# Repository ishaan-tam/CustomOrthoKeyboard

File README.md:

# CustomOrthoKeyboard

A customizable 4x12 ortholinear keyboard powered by Zephyr RTOS, with support for custom shields, layouts, and future expansions.

## Features
- 4x12 ortholinear layout
- Zephyr-based firmware
- Custom keymaps and debounce tuning
- QMK-inspired structure
- USB input with hot-plug detection

## Folder Overview
- `boards/shields/`: Custom shield definitions and pin configs
- `config/`: Keymap and build configs for the keyboard
- `zephyr/`: Zephyr OS base setup
- `build.yaml`: Build process definition

## Getting Started
To build the firmware:
```bash
west init -l .
west update
west build -b <your_board> -p

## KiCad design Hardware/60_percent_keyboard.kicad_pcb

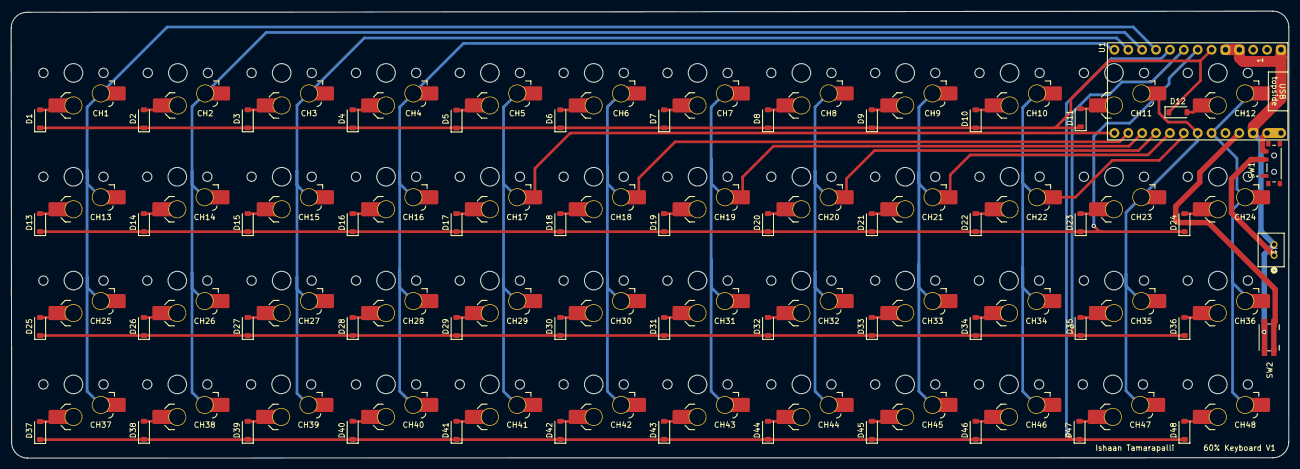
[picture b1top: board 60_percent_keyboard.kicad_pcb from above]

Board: 2 copper layers, 233.8 x 81.8 mm, 100 parts (0 on the bottom side), 68 nets.

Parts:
CH1, CH2, CH3, CH4, CH5, CH6, CH7, CH8, CH9, CH10, CH11, CH12, CH13, CH14, CH15, CH16, CH17, CH18, CH19, CH20, CH21, CH22, CH23, CH24, CH25, CH26, CH27, CH28, CH29, CH30, CH31, CH32, CH33, CH34, CH35, CH36, CH37, CH38, CH39, CH40, CH41, CH42, CH43, CH44, CH45, CH46, CH47, CH48: choc_SW_solder; SW_choc_v1_HS_1u
D1, D2, D3, D4, D5, D6, D7, D8, D9, D10, D11, D12, D13, D14, D15, D16, D17, D18, D19, D20, D21, D22, D23, D24, D25, D26, D27, D28, D29, D30, D31, D32, D33, D34, D35, D36, D37, D38, D39, D40, D41, D42, D43, D44, D45, D46, D47, D48: D; D_SOD-123
J1: Conn_01x02_Socket; CONN2_B2B-PH-K-S_JST
SW1: SW_SPDT; SW_EG1215AA
SW2: SW_Push; Panasonic_EVQPUJ_EVQPUA
U1: nice_nano; nice_nano_AH_USBup

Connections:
BAT+: SW1.3 (C), U1.13 (BAT+), U1.29 (BAT+)
GND: J1.2, SW2.2, U1.3 (GND), U1.4 (GND), U1.14 (GND), U1.28 (GND)
unnamed: CH1.2, D1.2 (A)
unnamed: CH2.2, D2.2 (A)
unnamed: CH3.2, D3.2 (A)
unnamed: CH4.2, D4.2 (A)
unnamed: CH5.2, D5.2 (A)
unnamed: CH6.2, D6.2 (A)
unnamed: CH7.2, D7.2 (A)
unnamed: CH8.2, D8.2 (A)
unnamed: CH9.2, D9.2 (A)
unnamed: CH10.2, D10.2 (A)
unnamed: CH11.2, D11.2 (A)
unnamed: CH12.2, D12.2 (A)
unnamed: CH13.2, D13.2 (A)
unnamed: CH14.2, D14.2 (A)
unnamed: CH15.2, D15.2 (A)
unnamed: CH16.2, D16.2 (A)
unnamed: CH17.2, D17.2 (A)
unnamed: CH18.2, D18.2 (A)
unnamed: CH19.2, D19.2 (A)
unnamed: CH20.2, D20.2 (A)
unnamed: CH21.2, D21.2 (A)
unnamed: CH22.2, D22.2 (A)
unnamed: CH23.2, D23.2 (A)
unnamed: CH24.2, D24.2 (A)
unnamed: CH25.2, D25.2 (A)
unnamed: CH26.2, D26.2 (A)
unnamed: CH27.2, D27.2 (A)
unnamed: CH28.2, D28.2 (A)
unnamed: CH29.2, D29.2 (A)
unnamed: CH30.2, D30.2 (A)
unnamed: CH31.2, D31.2 (A)
unnamed: CH32.2, D32.2 (A)
unnamed: CH33.2, D33.2 (A)
unnamed: CH34.2, D34.2 (A)
unnamed: CH35.2, D35.2 (A)
unnamed: CH36.2, D36.2 (A)
unnamed: CH37.2, D37.2 (A)
unnamed: CH38.2, D38.2 (A)
unnamed: CH39.2, D39.2 (A)
unnamed: CH40.2, D40.2 (A)
unnamed: CH41.2, D41.2 (A)
unnamed: CH42.2, D42.2 (A)
unnamed: CH43.2, D43.2 (A)
unnamed: CH44.2, D44.2 (A)
unnamed: CH45.2, D45.2 (A)
unnamed: CH46.2, D46.2 (A)
unnamed: CH47.2, D47.2 (A)
unnamed: CH48.2, D48.2 (A)
RAW: J1.1, SW1.2 (B)
RST: SW2.1, U1.15 (RST)
col1: CH1.1, CH13.1, CH25.1, CH37.1, U1.9 (P1.00)
col2: CH2.1, CH14.1, CH26.1, CH38.1, U1.10 (P0.11)
col3: CH3.1, CH15.1, CH27.1, CH39.1, U1.11 (P1.04-LF)
col4: CH4.1, CH16.1, CH28.1, CH40.1, U1.12 (P1.06-LF)
col5: CH5.1, CH17.1, CH29.1, CH41.1, U1.24 (P0.09-LF)
col6: CH6.1, CH18.1, CH30.1, CH42.1, U1.23 (P0-10-LF)
col7: CH7.1, CH19.1, CH31.1, CH43.1, U1.22 (P1.11-LF)
col8: CH8.1, CH20.1, CH32.1, CH44.1, U1.21 (P1.13-LF)
col9: CH9.1, CH21.1, CH33.1, CH45.1, U1.20 (P1.15-LF)
col10: CH10.1, CH22.1, CH34.1, CH46.1, U1.19 (P0.02-LF)
col11: CH11.1, CH23.1, CH35.1, CH47.1, U1.18 (P0.29-LF)
col12: CH12.1, CH24.1, CH36.1, CH48.1, U1.17 (P0.31-LF)
row1: D1.1 (K), D2.1 (K), D3.1 (K), D4.1 (K), D5.1 (K), D6.1 (K), D7.1 (K), D8.1 (K), D9.1 (K), D10.1 (K), D11.1 (K), D12.1 (K), U1.5 (P0.17)
row2: D13.1 (K), D14.1 (K), D15.1 (K), D16.1 (K), D17.1 (K), D18.1 (K), D19.1 (K), D20.1 (K), D21.1 (K), D22.1 (K), D23.1 (K), D24.1 (K), U1.6 (P0.20)
row3: D25.1 (K), D26.1 (K), D27.1 (K), D28.1 (K), D29.1 (K), D30.1 (K), D31.1 (K), D32.1 (K), D33.1 (K), D34.1 (K), D35.1 (K), D36.1 (K), U1.7 (P0.22)
row4: D37.1 (K), D38.1 (K), D39.1 (K), D40.1 (K), D41.1 (K), D42.1 (K), D43.1 (K), D44.1 (K), D45.1 (K), D46.1 (K), D47.1 (K), D48.1 (K), U1.8 (P0.24)

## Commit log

2024-07-27 Initial User Config.
2024-07-27 small change
2024-07-27 added files
2024-07-27 more changes
2024-07-27 added more files
2024-07-27 naming fix
2024-07-28 simplified to a 2x4 matrix
2024-07-28 simplified to a 2x4 matrix, used gpt this time
2024-07-28 back to known good
2024-07-28 changed to row2col
2024-07-28 changed pin assignments
2024-07-28 reverted back
2024-07-28 switched col and rows
2024-07-28 single key
2024-07-28 single key (fixed col and row assignemnt)
2024-07-28 swapped rows and columns
2024-07-28 swapped rows and colums
2024-07-28 trying differnt pins
2024-07-28 changed row to GPIO_ACTIVE_HIGH | GPIO_PULL_DOWN
2024-07-28 chagned pin number
2024-07-28 pins look right, changed to row2col
2024-07-28 swapped pull down for rows and cols
2024-07-28 keyboard worked only when connected to a multimeter set to continuity at the same time
2024-07-28 changed to 2x4 matrix
2024-07-28 fixed no of declared rows
2024-07-28 fixed row and col gpios
2024-07-28 changed to 2x3 matrix
2024-07-28 trying top right key
2024-07-28 trying row-gpio active high
2024-07-28 changed to col2row
2024-07-28 trying different pin
2024-07-28 changed pin again
2024-07-28 changed col to pull up
2024-09-30 reverted back to a state where w a s works
2024-10-01 added the extra two rows in the keymap file
2024-10-01 added two more rows for four rows total
2024-10-01 swapped rows and colums V2 previous commit does not work
2024-10-01 reverting to known good 4x4 config
2024-10-01 taking transpose of the 4x4 map
2024-10-01 row reverse the 4x4 transpose
2024-10-01 previous commit worked, added extra column
2024-10-01 previous commit worked, added extra column, prev had typo
2024-10-01 created a 4x12 matrix with keybinds
2024-10-01 created a 4x12 matrix with keybinds, changed keymap
2024-10-01 created a 4x6 matrix
2024-10-01 switched to known good 4x5 matrix
2024-10-01 switched to known good 4x5 matrix, changed keymap file
2024-10-01 4x5 matrix different approach
2024-10-01 4x6 matrix, used ZMK documentation this time
2024-10-01 4x8 matrix
2024-10-01 4x12 keyboard
2025-07-10 Added hardware folder
2025-07-11 created enclosure stl files
2025-07-16 testing to see if it still compiles
2025-07-16 swapped rows and colums and changed the map
2025-07-16 reverted back to origianl layout and added two more cols
